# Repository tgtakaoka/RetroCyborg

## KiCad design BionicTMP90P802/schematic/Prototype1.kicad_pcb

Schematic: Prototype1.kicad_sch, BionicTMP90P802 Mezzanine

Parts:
C1: 0.1u; C_Disc_D3.4mm_W2.1mm_P2.50mm
J1: BionicConnector; DIP-48_W7.62mm
U1: TMP90P802A; DIP-40_W15.24mm
U2: 74HCT126; DIP-14_W7.62mm

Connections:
/P10: J1.2 (P10), U1.12 (D0)
/P11: J1.3 (P11), U1.13 (D1)
/P12: J1.4 (P12), U1.14 (D2)
/P13: J1.5 (P13), U1.15 (D3)
/P14: J1.6 (P14), U1.16 (D4)
/P15: J1.7 (P15), U1.17 (D5)
/P16: J1.8 (P16), U1.18 (D6)
/P17: J1.9 (P17), U1.19 (D7)
/P20: J1.47 (P20), U1.24 (A0)
/P21: J1.46 (P21), U1.25 (A1)
/P22: J1.45 (P22), U1.26 (A2)
/P23: J1.44 (P23), U1.27 (A3)
/P24: J1.43 (P24), U1.28 (A4)
/P25: J1.42 (P25), U1.29 (A5)
/P26: J1.41 (P26), U1.30 (A6)
/P27: J1.40 (P27), U1.31 (A7)
/P30: J1.11 (P30), U1.32 (A8)
/P31: J1.12 (P31), U1.33 (A9)
/P32: J1.13 (P32), U1.34 (A10)
/P33: J1.14 (P33), U1.35 (A11)
/P34: J1.15 (P34), U1.36 (A12)
/P35: J1.16 (P35), U1.37 (A13)
/P36: J1.17 (P36), U1.38 (A14)
/P37: J1.18 (P37), U1.39 (A15)
/P40: J1.38 (P40), U1.7 (~INT1)
/P42: J1.36 (P42), U2.5 (2A)
/P43: J1.35 (P43), U2.9 (3A)
/P44: J1.34 (P44), U1.1 (RxD)
/P45: J1.33 (P45), U1.3 (TxD)
/P46: J1.32 (P46), U2.2 (1A)
/P47: J1.31 (P47), U1.11 (CLK)
/P50: J1.20 (P50), U1.4 (~RD)
/P51: J1.21 (P51), U1.5 (~WR)
/P52: J1.22 (P52), U1.6 (~WAIT)
/P53: J1.23 (P53), U2.12 (4A)
GND: C1.2, J1.1 (GND), J1.48 (GND), U1.10 (~EA), U1.20 (GND), U2.7 (GND)
unnamed: U1.8 (~INT0), U2.6 (2Y)
unnamed: U1.9 (~NMI), U2.8 (3Y)
unnamed: U1.21 (X1), U2.3 (1Y)
unnamed: U1.23 (~RESET), U2.11 (4Y)
VCC: C1.1, J1.24 (VCC), J1.25 (VCC), U1.40 (VCC), U2.1 (1OE), U2.4 (2OE), U2.10 (3OE), U2.13 (4OE), U2.14 (VCC)

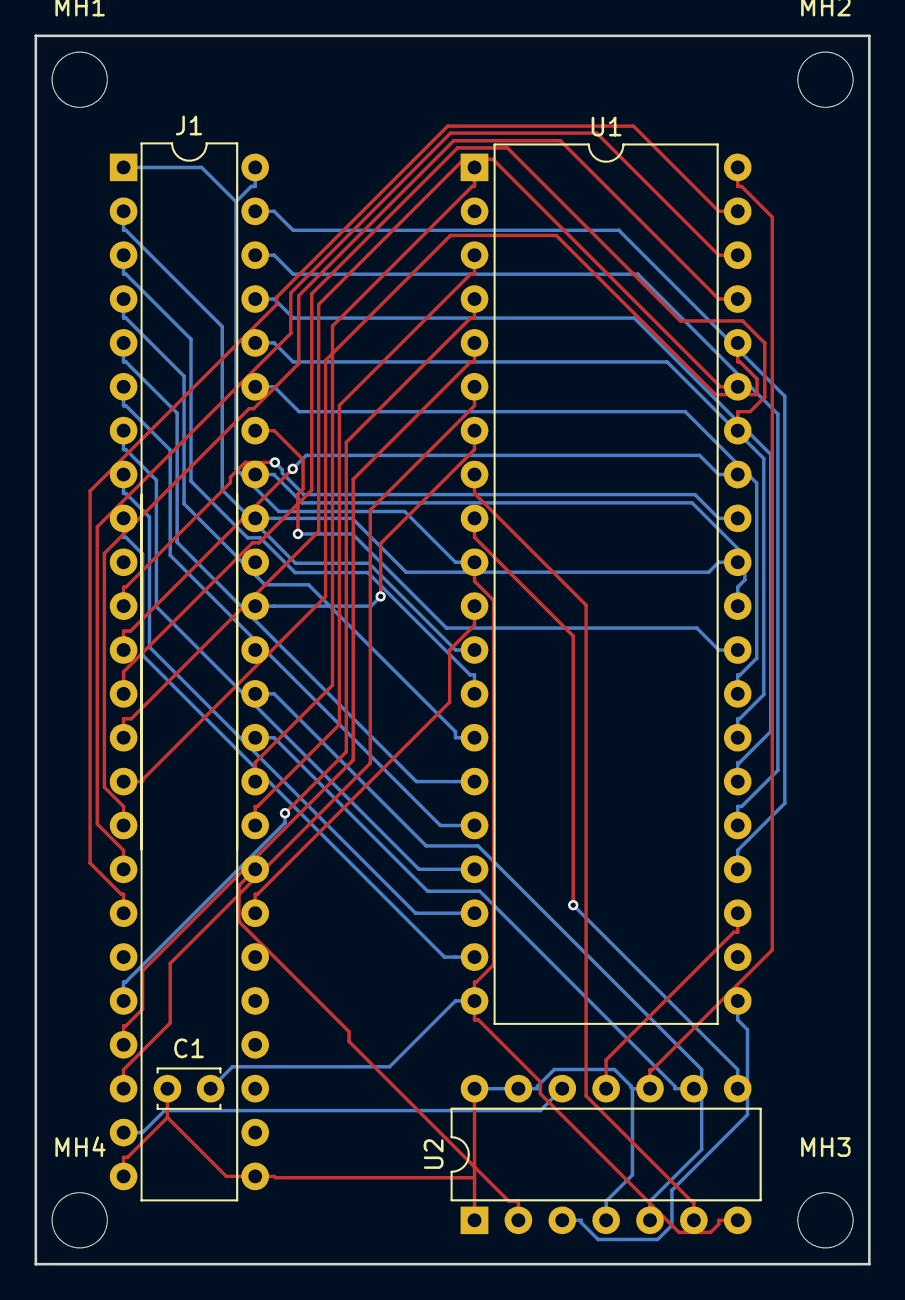
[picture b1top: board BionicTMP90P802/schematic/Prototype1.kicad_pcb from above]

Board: 2 copper layers, 48.3 x 71.1 mm, 8 parts (0 on the bottom side), 41 nets.

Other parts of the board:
MH1, MH2, MH3, MH4: MountingHole_3.2mm_M3

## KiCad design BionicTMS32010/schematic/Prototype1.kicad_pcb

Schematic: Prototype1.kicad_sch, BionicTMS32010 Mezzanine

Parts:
C1: 0.1u; C_Disc_D3.4mm_W2.1mm_P2.50mm
J1: BionicConnector; DIP-48_W7.62mm
U1: TMS32C010NL; DIP-40_W15.24mm
U2: 74HCT126; DIP-14_W7.62mm

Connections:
/P10: J1.2 (P10), U1.26 (D0)
/P11: J1.3 (P11), U1.25 (D1)
/P12: J1.4 (P12), U1.24 (D2)
/P13: J1.5 (P13), U1.23 (D3)
/P14: J1.6 (P14), U1.22 (D4)
/P15: J1.7 (P15), U1.21 (D5)
/P16: J1.8 (P16), U1.20 (D6)
/P17: J1.9 (P17), U1.19 (D7)
/P20: J1.47 (P20), U1.11 (D8)
/P21: J1.46 (P21), U1.12 (D9)
/P22: J1.45 (P22), U1.13 (D10)
/P23: J1.44 (P23), U1.14 (D11)
/P24: J1.43 (P24), U1.15 (D12)
/P25: J1.42 (P25), U1.16 (D13)
/P26: J1.41 (P26), U1.17 (D14)
/P27: J1.40 (P27), U1.18 (D15)
/P30: J1.11 (P30), U1.2 (A0/PA0)
/P31: J1.12 (P31), U1.1 (A1/PA1)
/P32: J1.13 (P32), U1.40 (A2/PA2)
/P33: J1.14 (P33), U1.39 (A3)
/P34: J1.15 (P34), U1.38 (A4)
/P35: J1.16 (P35), U1.37 (A5)
/P36: J1.17 (P36), U1.36 (A6)
/P37: J1.18 (P37), U1.35 (A7)
/P40: J1.38 (P40), U1.34 (A8)
/P41: J1.37 (P41), U1.29 (A9)
/P42: J1.36 (P42), U1.28 (A10)
/P43: J1.35 (P43), U1.27 (A11)
/P44: J1.34 (P44), U1.5 (~INT)
/P45: J1.33 (P45), U1.9 (~BIO)
/P46: J1.32 (P46), U2.2 (1A)
/P47: J1.31 (P47), U1.6 (CLKOUT)
/P50: J1.20 (P50), U1.32 (~DEN)
/P51: J1.21 (P51), U1.31 (~WE)
/P52: J1.22 (P52), U1.33 (~MEN)
/P53: J1.23 (P53), U1.4 (~RS)
GND: C1.2, J1.1 (GND), J1.48 (GND), U1.3 (MC/~MP), U1.10 (VSS), U2.4 (2OE), U2.5 (2A), U2.7 (GND), U2.9 (3A), U2.10 (3OE), U2.12 (4A), U2.13 (4OE)
unnamed: U1.8 (X2/CLKIN), U2.3 (1Y)
VCC: C1.1, J1.24 (VCC), J1.25 (VCC), U1.30 (VCC), U2.1 (1OE), U2.14 (VCC)

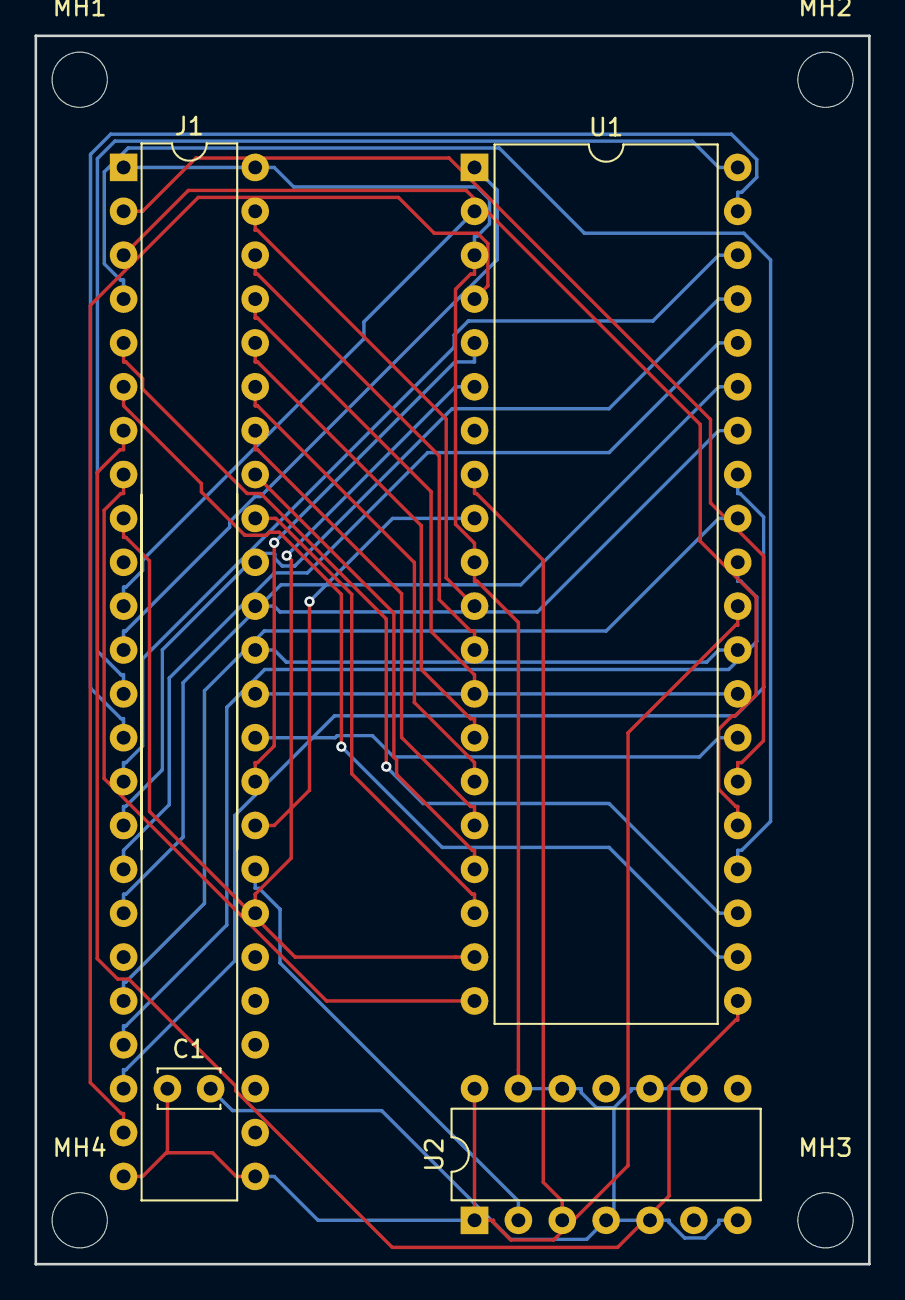
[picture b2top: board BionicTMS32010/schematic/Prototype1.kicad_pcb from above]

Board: 2 copper layers, 48.3 x 71.1 mm, 8 parts (0 on the bottom side), 39 nets.

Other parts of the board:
MH1, MH2, MH3, MH4: MountingHole_3.2mm_M3

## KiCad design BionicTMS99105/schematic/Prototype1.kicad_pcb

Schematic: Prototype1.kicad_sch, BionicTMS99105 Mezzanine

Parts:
C1: 0.1u; C_Disc_D3.4mm_W2.1mm_P2.50mm
J1: BionicConnector; DIP-48_W7.62mm
U1: TMS99105; DIP-40_W15.24mm
U2: 74HCT126; DIP-14_W7.62mm

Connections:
/P10: J1.2 (P10), U1.31 (D15)
/P11: J1.3 (P11), U1.30 (AD14)
/P12: J1.4 (P12), U1.29 (AD13)
/P13: J1.5 (P13), U1.28 (AD12)
/P14: J1.6 (P14), U1.27 (AD11)
/P15: J1.7 (P15), U1.26 (AD10)
/P16: J1.8 (P16), U1.25 (AD9)
/P17: J1.9 (P17), U1.24 (AD8)
/P20: J1.47 (P20), U1.23 (AD7)
/P21: J1.46 (P21), U1.22 (AD6)
/P22: J1.45 (P22), U1.21 (AD5)
/P23: J1.44 (P23), U1.20 (AD4)
/P24: J1.43 (P24), U1.19 (AD3)
/P25: J1.42 (P25), U1.18 (AD2)
/P26: J1.41 (P26), U1.17 (AD1)
/P27: J1.40 (P27), U1.16 (AD0)
/P30: J1.11 (P30), U1.37 (BST3)
/P31: J1.12 (P31), U1.38 (BST2)
/P32: J1.13 (P32), U1.39 (BST1)
/P34: J1.15 (P34), U1.13 (IC3)
/P35: J1.16 (P35), U1.12 (IC2)
/P36: J1.17 (P36), U1.11 (IC1)
/P37: J1.18 (P37), U1.10 (IC0)
/P40: J1.38 (P40), U1.5 (~HOLD)
/P41: J1.37 (P41), U1.4 (~APP)
/P42: J1.36 (P42), U1.8 (~INTREQ)
/P43: J1.35 (P43), U1.9 (~NMI)
/P44: J1.34 (P44), U1.32 (ALATCH)
/P45: J1.33 (P45), U1.14 (R/~W)
/P46: J1.32 (P46), U2.2 (1A)
/P47: J1.31 (P47), U1.34 (CLKOUT)
/P50: J1.20 (P50), U1.2 (~RD)
/P51: J1.21 (P51), U1.1 (~WE)
/P52: J1.22 (P52), U1.7 (READY)
/P53: J1.23 (P53), U1.3 (~RESET)
/P54: J1.29 (P54), U1.40 (~MEM)
GND: C1.2, J1.1 (GND), J1.48 (GND), U1.6 (VSS), U1.33 (VSS), U2.4 (2OE), U2.5 (2A), U2.7 (GND), U2.9 (3A), U2.10 (3OE), U2.12 (4A), U2.13 (4OE)
unnamed: U1.36 (CLKIN), U2.3 (1Y)
VCC: C1.1, J1.24 (VCC), J1.25 (VCC), U1.15 (VCC), U2.1 (1OE), U2.14 (VCC)

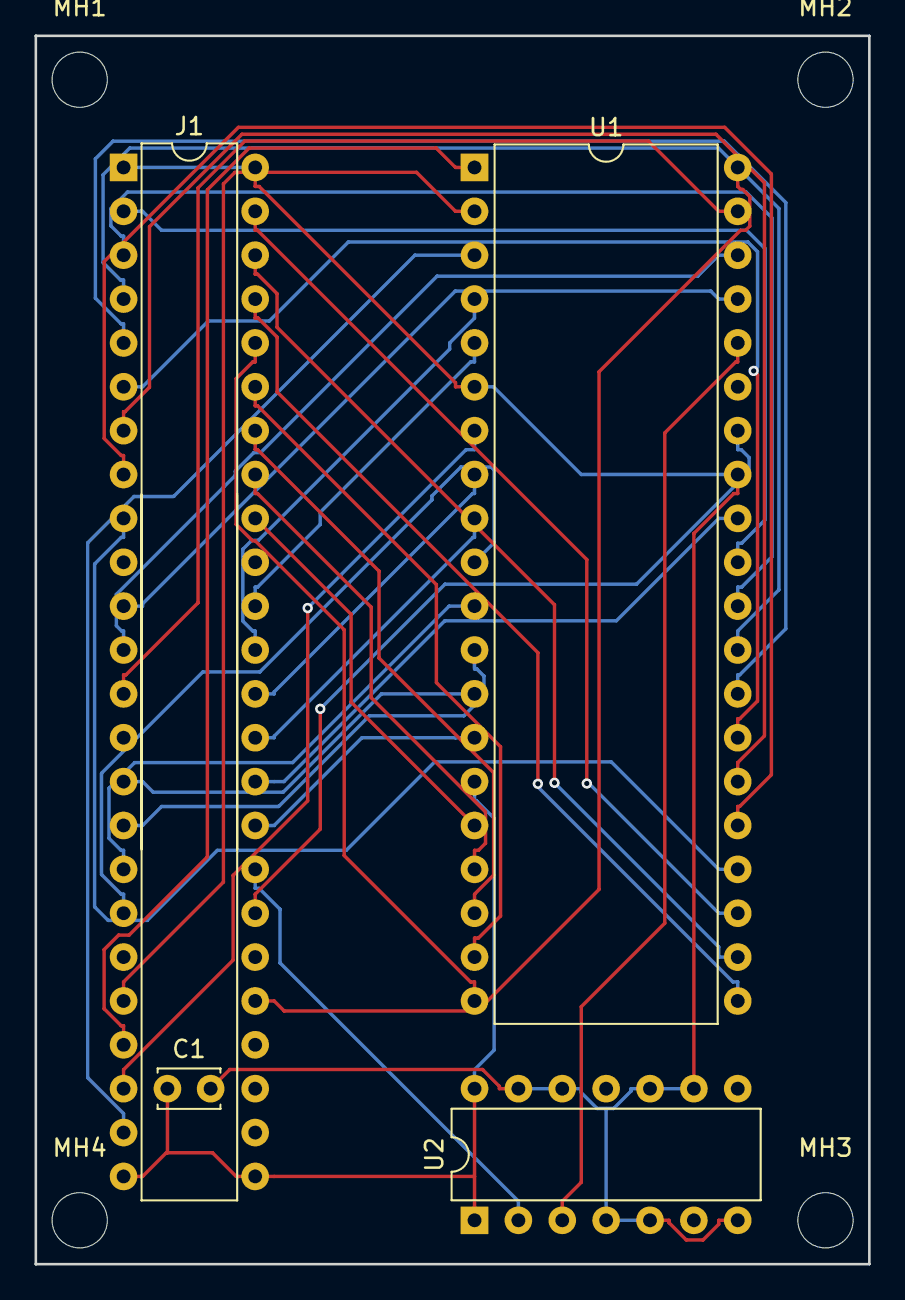
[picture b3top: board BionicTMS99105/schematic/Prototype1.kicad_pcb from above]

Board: 2 copper layers, 48.3 x 71.1 mm, 8 parts (0 on the bottom side), 39 nets.

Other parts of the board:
MH1, MH2, MH3, MH4: MountingHole_3.2mm_M3

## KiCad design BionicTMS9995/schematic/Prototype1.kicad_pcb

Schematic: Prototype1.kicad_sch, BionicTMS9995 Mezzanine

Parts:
C1: 0.1u; C_Disc_D3.4mm_W2.1mm_P2.50mm
J1: BionicConnector; DIP-48_W7.62mm
U1: TMS9995; DIP-40_W15.24mm
U2: 74HCT126; DIP-14_W7.62mm

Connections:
/P10: J1.2 (P10), U1.4 (D7)
/P11: J1.3 (P11), U1.5 (D6)
/P12: J1.4 (P12), U1.6 (D5)
/P13: J1.5 (P13), U1.7 (D4)
/P14: J1.6 (P14), U1.8 (D3)
/P15: J1.7 (P15), U1.9 (D2)
/P16: J1.8 (P16), U1.11 (D1)
/P17: J1.9 (P17), U1.12 (D0)
/P20: J1.47 (P20), U1.40 (A15)
/P21: J1.46 (P21), U1.39 (A14)
/P22: J1.45 (P22), U1.38 (A13)
/P23: J1.44 (P23), U1.37 (A12)
/P24: J1.43 (P24), U1.36 (A11)
/P25: J1.42 (P25), U1.35 (A10)
/P26: J1.41 (P26), U1.34 (A9)
/P27: J1.40 (P27), U1.33 (A8)
/P30: J1.11 (P30), U1.32 (A7)
/P31: J1.12 (P31), U1.30 (A6)
/P32: J1.13 (P32), U1.29 (A5)
/P33: J1.14 (P33), U1.28 (A4)
/P34: J1.15 (P34), U1.27 (A3)
/P35: J1.16 (P35), U1.26 (A2)
/P36: J1.17 (P36), U1.25 (A1)
/P37: J1.18 (P37), U1.24 (A0)
/P40: J1.38 (P40), U1.18 (~HOLD)
/P42: J1.36 (P42), U1.15 (~INT1)
/P43: J1.35 (P43), U1.21 (~NMI)
/P44: J1.34 (P44), U1.14 (~INT4)
/P45: J1.33 (P45), U1.13 (CRUIN)
/P46: J1.32 (P46), U2.2 (1A)
/P47: J1.31 (P47), U1.3 (CLKOUT)
/P50: J1.20 (P50), U1.17 (~DBIN)
/P51: J1.21 (P51), U1.19 (~WE)
/P52: J1.22 (P52), U1.23 (READY)
/P53: J1.23 (P53), U1.22 (~RESET)
/P54: J1.29 (P54), U1.20 (~MEMEN)
/P55: J1.28 (P55), U1.16 (IAQ)
GND: C1.2, J1.1 (GND), J1.48 (GND), U1.31 (VSS), U2.4 (2OE), U2.5 (2A), U2.7 (GND), U2.9 (3A), U2.10 (3OE), U2.12 (4A), U2.13 (4OE)
unnamed: U1.2 (CLKIN), U2.3 (1Y)
VCC: C1.1, J1.24 (VCC), J1.25 (VCC), U1.10 (VCC), U2.1 (1OE), U2.14 (VCC)

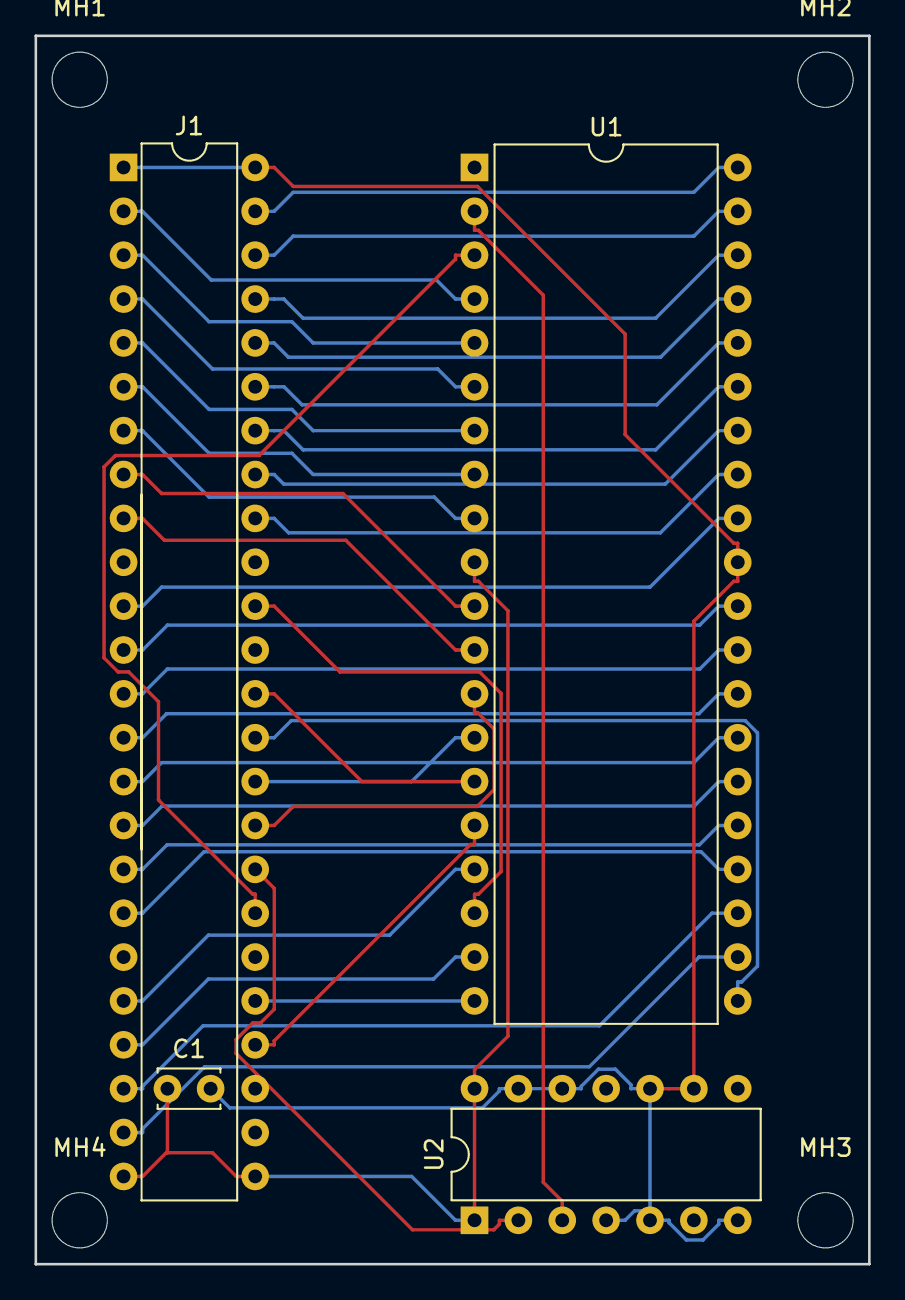
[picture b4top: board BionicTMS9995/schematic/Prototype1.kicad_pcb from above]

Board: 2 copper layers, 48.3 x 71.1 mm, 8 parts (0 on the bottom side), 40 nets.

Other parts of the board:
MH1, MH2, MH3, MH4: MountingHole_3.2mm_M3

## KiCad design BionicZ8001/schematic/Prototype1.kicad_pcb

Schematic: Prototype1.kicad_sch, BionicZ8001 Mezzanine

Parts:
C1, C2, C3, C4: 0.1u; C_Disc_D3.4mm_W2.1mm_P2.50mm
J1: BionicConnector; DIP-48_W7.62mm
U1: Z8001; DIP-48_W15.24mm
U2: 74HCT126; DIP-14_W7.62mm
U3, U4: 74HCT541; DIP-20_W7.62mm

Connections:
/P10: J1.2 (P10), U1.1 (AD0)
/P11: J1.3 (P11), U1.38 (AD1)
/P12: J1.4 (P12), U1.39 (AD2)
/P13: J1.5 (P13), U1.40 (AD3)
/P14: J1.6 (P14), U1.43 (AD4)
/P15: J1.7 (P15), U1.41 (AD5)
/P16: J1.8 (P16), U1.44 (AD6)
/P17: J1.9 (P17), U1.45 (AD7)
/P20: J1.47 (P20), U1.48 (AD8)
/P21: J1.46 (P21), U1.2 (AD9)
/P22: J1.45 (P22), U1.3 (AD10)
/P23: J1.44 (P23), U1.4 (AD11)
/P24: J1.43 (P24), U1.5 (AD12)
/P25: J1.42 (P25), U1.6 (AD13)
/P26: J1.41 (P26), U1.10 (AD14)
/P27: J1.40 (P27), U1.9 (AD15)
/P30: J1.11 (P30), U3.18 (Y0), U4.18 (Y0)
/P31: J1.12 (P31), U3.17 (Y1), U4.17 (Y1)
/P32: J1.13 (P32), U3.16 (Y2), U4.16 (Y2)
/P33: J1.14 (P33), U3.15 (Y3), U4.15 (Y3)
/P34: J1.15 (P34), U3.14 (Y4), U4.14 (Y4)
/P35: J1.16 (P35), U3.13 (Y5), U4.13 (Y5)
/P36: J1.17 (P36), U3.12 (Y6), U4.12 (Y6)
/P37: J1.18 (P37), U1.27 (~BUSREQ)
/P40: J1.38 (P40), U1.34 (~AS)
/P41: J1.37 (P41), U1.30 (R/~W)
/P42: J1.36 (P42), U1.13 (~NVI)
/P43: J1.35 (P43), U2.5 (2A)
/P44: J1.34 (P44), U1.12 (~VI)
/P45: J1.33 (P45), U1.19 (~DS)
/P46: J1.32 (P46), U2.2 (1A)
/P47: J1.31 (P47), U1.18 (~MREQ)
/P50: J1.20 (P50), U1.14 (~SEGT)
/P51: J1.21 (P51), U1.7 (~STOP)
/P52: J1.22 (P52), U1.28 (~WAIT)
/P53: J1.23 (P53), U2.9 (3A)
/P54: J1.29 (P54), U4.1 (G1), U4.19 (G2)
/P55: J1.28 (P55), U3.1 (G1), U3.19 (G2)
GND: C1.2, C2.2, C3.2, C4.2, J1.1 (GND), J1.48 (GND), U1.36 (GND), U2.7 (GND), U2.12 (4A), U2.13 (4OE), U3.9 (A7), U3.10 (GND), U4.9 (A7), U4.10 (GND)
unnamed: U1.15 (~NMI), U2.6 (2Y)
unnamed: U1.16 (~RESET), U2.8 (3Y)
unnamed: U1.20 (ST3), U4.5 (A3)
unnamed: U1.21 (ST2), U4.4 (A2)
unnamed: U1.22 (ST1), U4.3 (A1)
unnamed: U1.23 (ST0), U4.2 (A0)
unnamed: U1.24 (SN3), U3.5 (A3)
unnamed: U1.25 (SN1), U3.3 (A1)
unnamed: U1.26 (SN0), U3.2 (A0)
unnamed: U1.29 (~BUSACK), U4.8 (A6)
unnamed: U1.31 (N/~S), U4.6 (A4)
unnamed: U1.32 (B/~W), U4.7 (A5)
unnamed: U1.35 (CLOCK), U2.3 (1Y)
unnamed: U1.37 (SN2), U3.4 (A2)
unnamed: U1.42 (SN4), U3.6 (A4)
unnamed: U1.46 (SN5), U3.7 (A5)
unnamed: U1.47 (SN6), U3.8 (A6)
VCC: C1.1, C2.1, C3.1, C4.1, J1.24 (VCC), J1.25 (VCC), U1.11 (VCC), U2.1 (1OE), U2.4 (2OE), U2.10 (3OE), U2.14 (VCC), U3.20 (VCC), U4.20 (VCC)

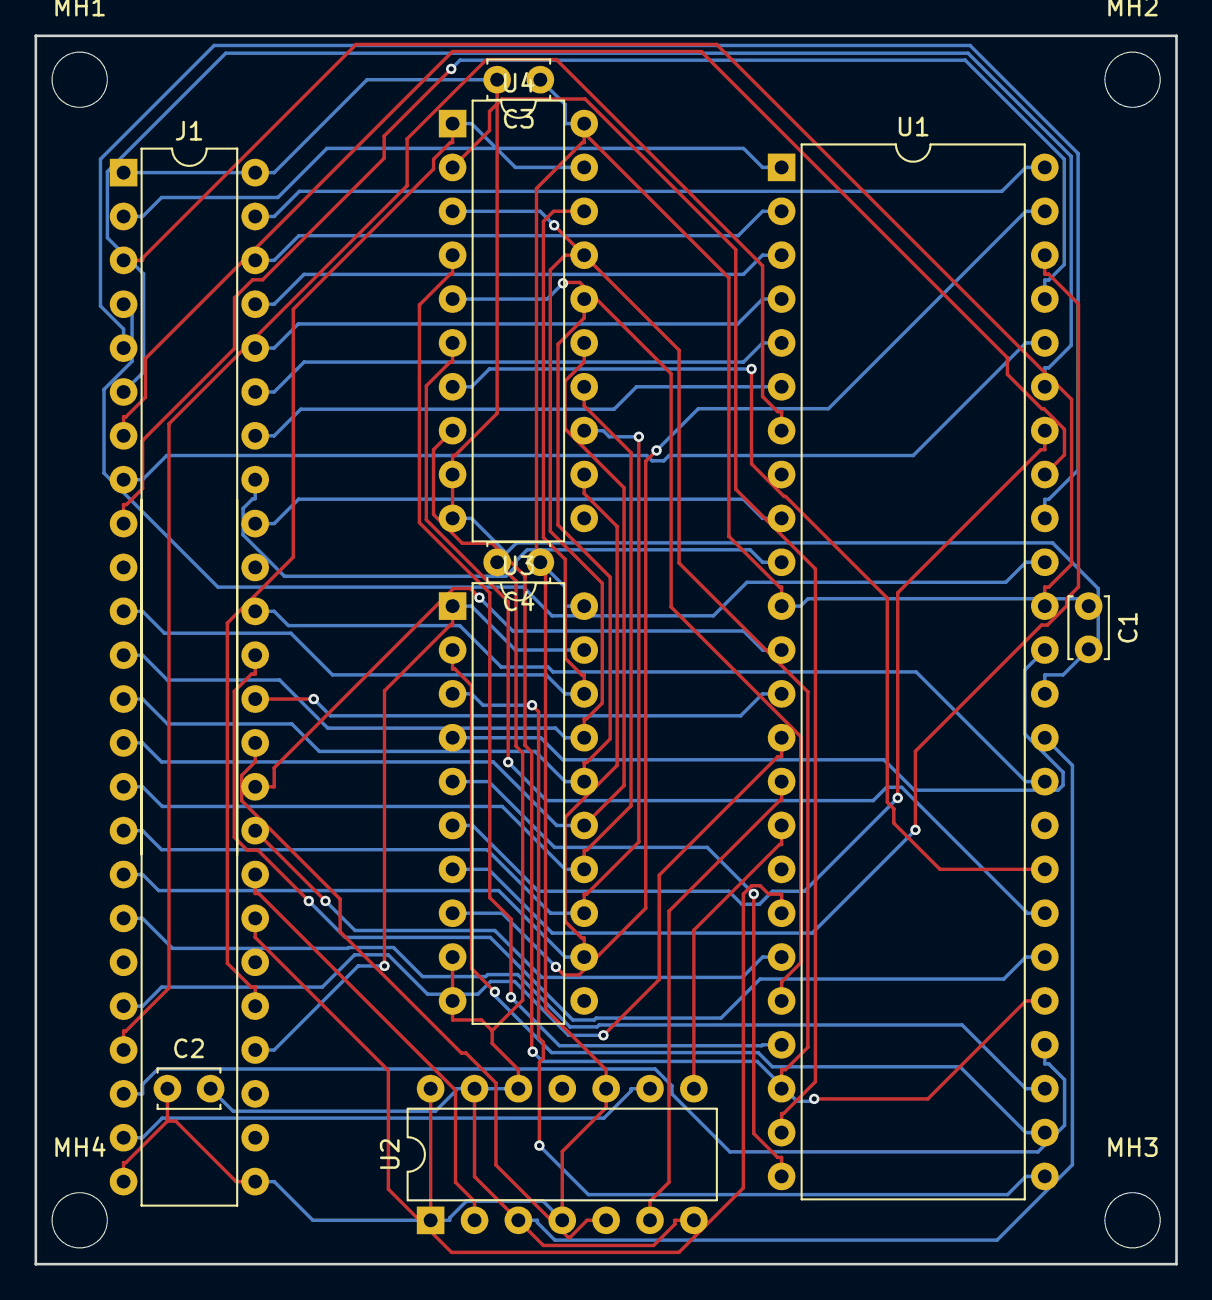
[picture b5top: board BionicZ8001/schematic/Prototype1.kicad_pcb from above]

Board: 2 copper layers, 66.0 x 71.1 mm, 13 parts (0 on the bottom side), 57 nets.

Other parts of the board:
MH1, MH2, MH3, MH4: MountingHole_3.2mm_M3

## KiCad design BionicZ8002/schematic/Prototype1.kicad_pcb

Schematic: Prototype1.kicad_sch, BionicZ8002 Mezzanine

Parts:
C1: 0.1u; C_Disc_D3.4mm_W2.1mm_P2.50mm
J1: BionicConnector; DIP-48_W7.62mm
U1: Z8002; DIP-40_W15.24mm
U2: 74HCT126; DIP-14_W7.62mm

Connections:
/P10: J1.2 (P10), U1.40 (AD0)
/P11: J1.3 (P11), U1.32 (AD1)
/P12: J1.4 (P12), U1.33 (AD2)
/P13: J1.5 (P13), U1.34 (AD3)
/P14: J1.6 (P14), U1.36 (AD4)
/P15: J1.7 (P15), U1.35 (AD5)
/P16: J1.8 (P16), U1.37 (AD6)
/P17: J1.9 (P17), U1.38 (AD7)
/P20: J1.47 (P20), U1.39 (AD8)
/P21: J1.46 (P21), U1.1 (AD9)
/P22: J1.45 (P22), U1.2 (AD10)
/P23: J1.44 (P23), U1.3 (AD11)
/P24: J1.43 (P24), U1.4 (AD12)
/P25: J1.42 (P25), U1.5 (AD13)
/P26: J1.41 (P26), U1.9 (AD14)
/P27: J1.40 (P27), U1.8 (AD15)
/P30: J1.11 (P30), U1.21 (ST0)
/P31: J1.12 (P31), U1.20 (ST1)
/P32: J1.13 (P32), U1.19 (ST2)
/P33: J1.14 (P33), U1.18 (ST3)
/P34: J1.15 (P34), U1.26 (N/~S)
/P35: J1.16 (P35), U1.27 (B/~W)
/P36: J1.17 (P36), U1.24 (~BUSACK)
/P37: J1.18 (P37), U1.22 (~BUSREQ)
/P40: J1.38 (P40), U1.29 (~AS)
/P41: J1.37 (P41), U1.25 (R/~W)
/P42: J1.36 (P42), U1.12 (~NVI)
/P43: J1.35 (P43), U2.5 (2A)
/P44: J1.34 (P44), U1.11 (~VI)
/P45: J1.33 (P45), U1.17 (~DS)
/P46: J1.32 (P46), U2.2 (1A)
/P47: J1.31 (P47), U1.16 (~MREQ)
/P51: J1.21 (P51), U1.6 (~STOP)
/P52: J1.22 (P52), U1.23 (~WAIT)
/P53: J1.23 (P53), U2.9 (3A)
/P54: J1.29 (P54), U1.15 (~MO)
/P55: J1.28 (P55), U1.7 (~MI)
GND: C1.2, J1.1 (GND), J1.48 (GND), U1.31 (GND), U2.7 (GND), U2.12 (4A), U2.13 (4OE)
unnamed: U1.13 (~NMI), U2.6 (2Y)
unnamed: U1.14 (~RESET), U2.8 (3Y)
unnamed: U1.30 (CLOCK), U2.3 (1Y)
VCC: C1.1, J1.24 (VCC), J1.25 (VCC), U1.10 (VCC), U2.1 (1OE), U2.4 (2OE), U2.10 (3OE), U2.14 (VCC)

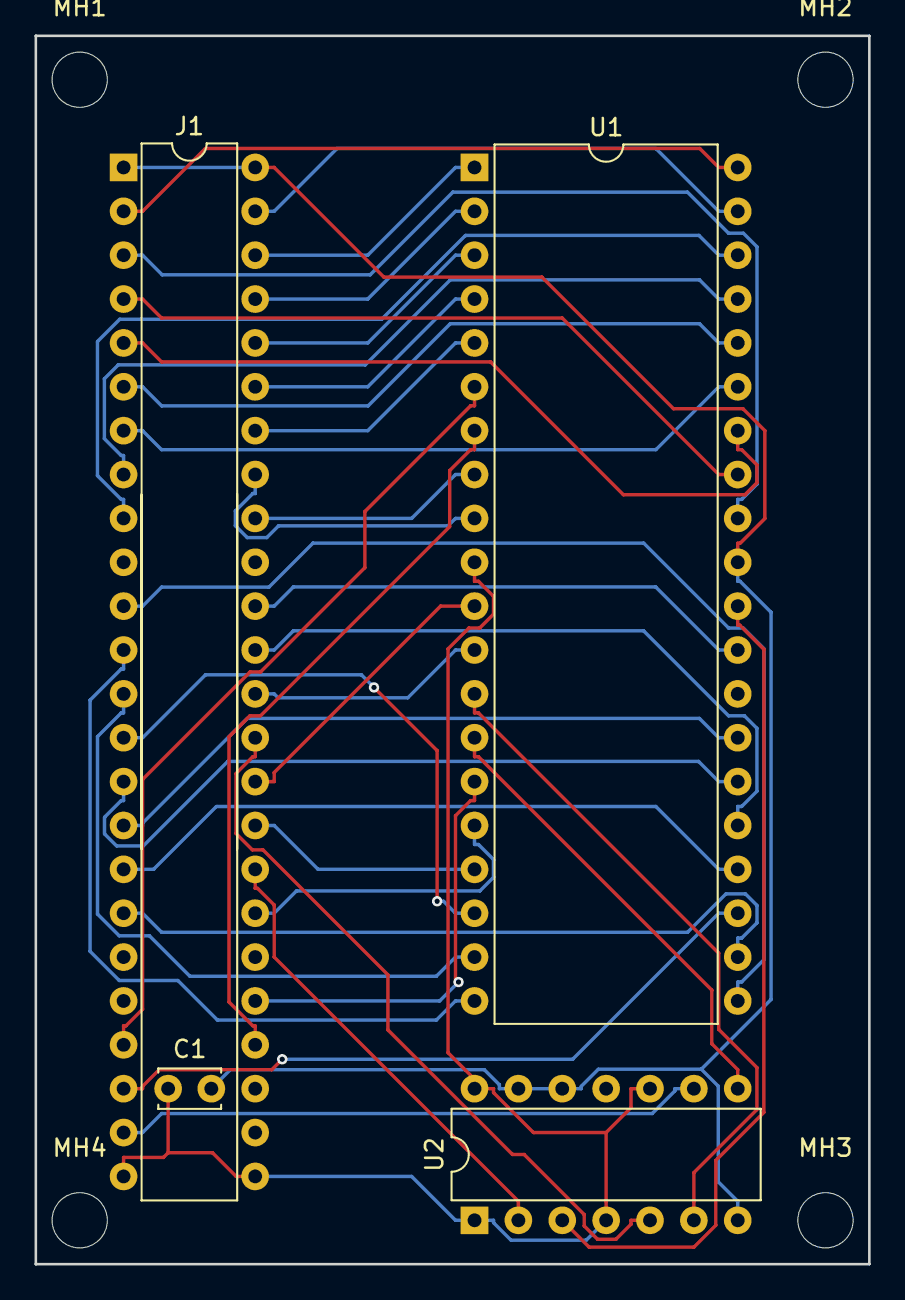
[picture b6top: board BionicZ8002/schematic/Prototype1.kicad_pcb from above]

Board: 2 copper layers, 48.3 x 71.1 mm, 8 parts (0 on the bottom side), 42 nets.

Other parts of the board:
MH1, MH2, MH3, MH4: MountingHole_3.2mm_M3

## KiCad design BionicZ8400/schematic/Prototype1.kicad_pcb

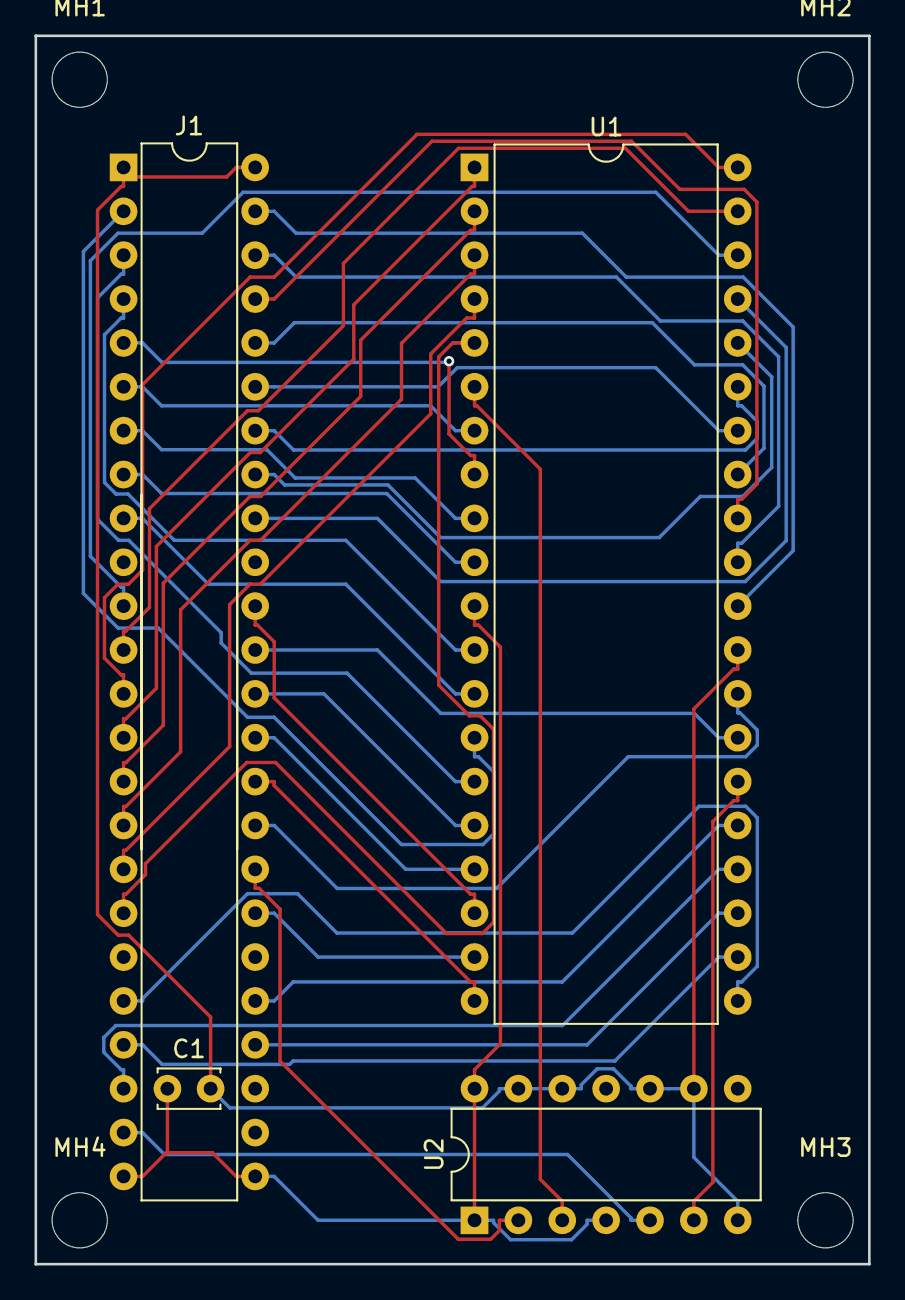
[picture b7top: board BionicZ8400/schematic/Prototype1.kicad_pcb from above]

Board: 2 copper layers, 48.3 x 71.1 mm, 8 parts (0 on the bottom side), 42 nets.

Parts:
C1: 0.1u; C_Disc_D3.4mm_W2.1mm_P2.50mm
J1: BionicConnector; DIP-48_W7.62mm
MH1, MH2, MH3, MH4: MountingHole_3.2mm_M3
U1: Z84C00; DIP-40_W15.24mm
U2: 74HCT126; DIP-14_W7.62mm

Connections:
/P10: J1.2, U1.14
/P11: J1.3, U1.15
/P12: J1.4, U1.12
/P13: J1.5, U1.8
/P14: J1.6, U1.7
/P15: J1.7, U1.9
/P16: J1.8, U1.10
/P17: J1.9, U1.13
/P20: J1.47, U1.30
/P21: J1.46, U1.31
/P22: J1.45, U1.32
/P23: J1.44, U1.33
/P24: J1.43, U1.34
/P25: J1.42, U1.35
/P26: J1.41, U1.36
/P27: J1.40, U1.37
/P30: J1.11, U1.38
/P31: J1.12, U1.39
/P32: J1.13, U1.40
/P33: J1.14, U1.1
/P34: J1.15, U1.2
/P35: J1.16, U1.3
/P36: J1.17, U1.4
/P37: J1.18, U1.5
/P40: J1.38, U1.18
/P41: J1.37, U1.27
/P42: J1.36, U1.16
/P43: J1.35, U1.17
/P44: J1.34, U1.20
/P45: J1.33, U1.28
/P46: J1.32, U2.2
/P47: J1.31, U1.19
/P50: J1.20, U1.21
/P51: J1.21, U1.22
/P52: J1.22, U1.24
/P53: J1.23, U2.5
/P54: J1.29, U1.25
/P55: J1.28, U1.23
GND: C1.2, J1.1, J1.48, U1.29, U2.7, U2.9, U2.10, U2.12, U2.13
unnamed: U1.6, U2.3
unnamed: U1.26, U2.6
VCC: C1.1, J1.24, J1.25, U1.11, U2.1, U2.4, U2.14

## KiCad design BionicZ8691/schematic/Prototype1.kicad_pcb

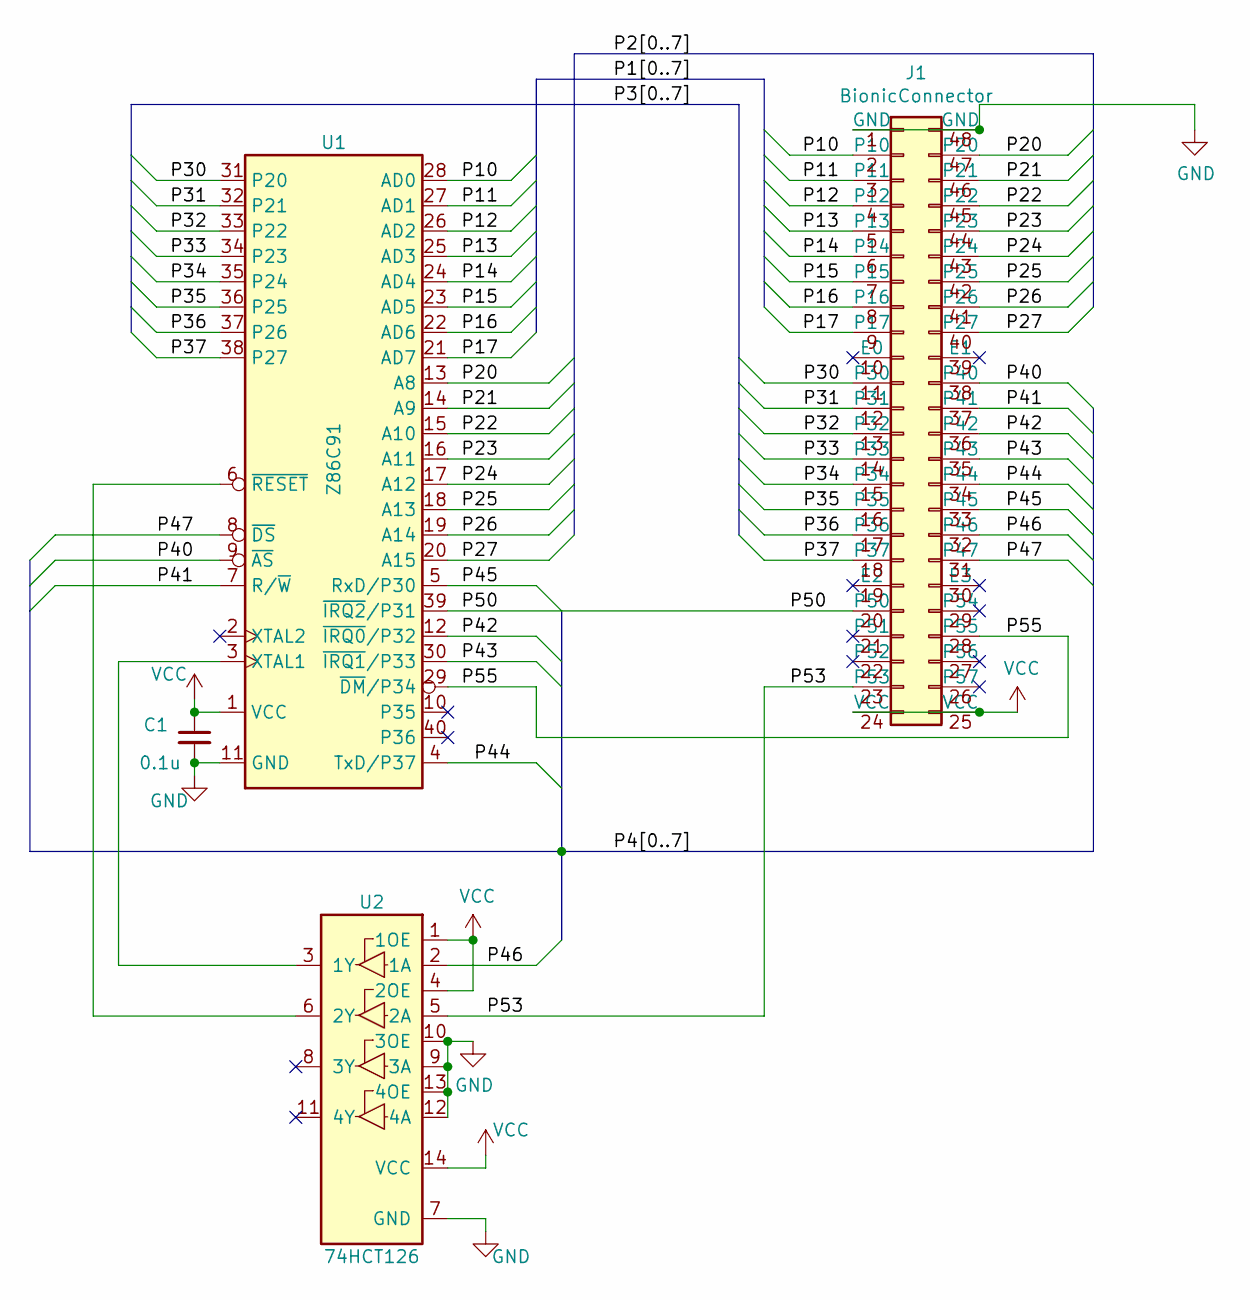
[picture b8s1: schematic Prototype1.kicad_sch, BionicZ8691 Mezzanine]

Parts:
C1: 0.1u; C_Disc_D3.4mm_W2.1mm_P2.50mm
J1: BionicConnector; DIP-48_W7.62mm
U1: Z86C91; DIP-40_W15.24mm
U2: 74HCT126; DIP-14_W7.62mm

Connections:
/P10: J1.2 (P10), U1.28 (AD0)
/P11: J1.3 (P11), U1.27 (AD1)
/P12: J1.4 (P12), U1.26 (AD2)
/P13: J1.5 (P13), U1.25 (AD3)
/P14: J1.6 (P14), U1.24 (AD4)
/P15: J1.7 (P15), U1.23 (AD5)
/P16: J1.8 (P16), U1.22 (AD6)
/P17: J1.9 (P17), U1.21 (AD7)
/P20: J1.47 (P20), U1.13 (A8)
/P21: J1.46 (P21), U1.14 (A9)
/P22: J1.45 (P22), U1.15 (A10)
/P23: J1.44 (P23), U1.16 (A11)
/P24: J1.43 (P24), U1.17 (A12)
/P25: J1.42 (P25), U1.18 (A13)
/P26: J1.41 (P26), U1.19 (A14)
/P27: J1.40 (P27), U1.20 (A15)
/P30: J1.11 (P30), U1.31 (P20)
/P31: J1.12 (P31), U1.32 (P21)
/P32: J1.13 (P32), U1.33 (P22)
/P33: J1.14 (P33), U1.34 (P23)
/P34: J1.15 (P34), U1.35 (P24)
/P35: J1.16 (P35), U1.36 (P25)
/P36: J1.17 (P36), U1.37 (P26)
/P37: J1.18 (P37), U1.38 (P27)
/P40: J1.38 (P40), U1.9 (~AS)
/P41: J1.37 (P41), U1.7 (R/~W)
/P42: J1.36 (P42), U1.12 (~IRQ0/P32)
/P43: J1.35 (P43), U1.30 (~IRQ1/P33)
/P44: J1.34 (P44), U1.4 (TxD/P37)
/P45: J1.33 (P45), U1.5 (RxD/P30)
/P46: J1.32 (P46), U2.2 (1A)
/P47: J1.31 (P47), U1.8 (~DS)
/P50: J1.20 (P50), U1.39 (~IRQ2/P31)
/P53: J1.23 (P53), U2.5 (2A)
/P55: J1.28 (P55), U1.29 (~DM/P34)
GND: C1.2, J1.1 (GND), J1.48 (GND), U1.11 (GND), U2.7 (GND), U2.9 (3A), U2.10 (3OE), U2.12 (4A), U2.13 (4OE)
unnamed: U1.3 (XTAL1), U2.3 (1Y)
unnamed: U1.6 (~RESET), U2.6 (2Y)
VCC: C1.1, J1.24 (VCC), J1.25 (VCC), U1.1 (VCC), U2.1 (1OE), U2.4 (2OE), U2.14 (VCC)

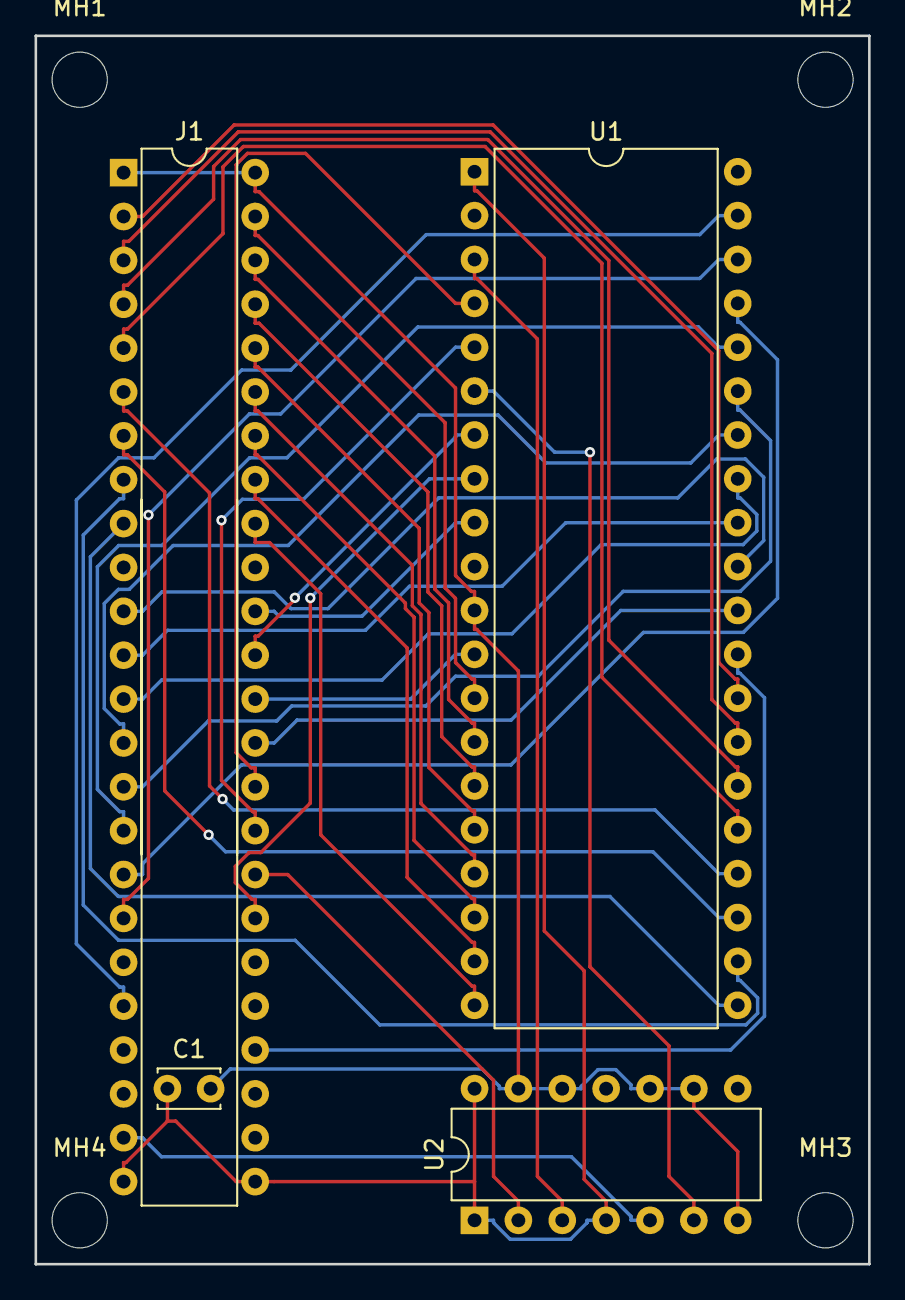
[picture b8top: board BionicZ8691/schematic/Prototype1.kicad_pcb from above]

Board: 2 copper layers, 48.3 x 71.1 mm, 8 parts (0 on the bottom side), 39 nets.

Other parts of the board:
MH1, MH2, MH3, MH4: MountingHole_3.2mm_M3
